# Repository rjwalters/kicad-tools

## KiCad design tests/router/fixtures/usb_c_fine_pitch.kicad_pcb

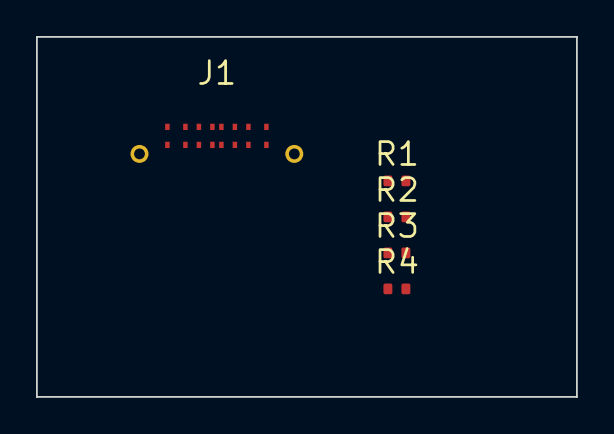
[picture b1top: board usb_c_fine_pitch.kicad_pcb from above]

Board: 4 copper layers, 30.0 x 20.0 mm, 5 parts (0 on the bottom side), 6 nets, no tracks yet.

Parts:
J1: USB-C; USB_C_Receptacle_GCT_USB4105
R1, R2: 0R; R_0402_1005Metric
R3, R4: 5k1; R_0402_1005Metric

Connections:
GND: J1.A1, J1.A12, J1.B1, J1.B12, J1.S1, J1.S2, R3.2, R4.2
USB_CC1: J1.A5, R3.1
USB_CC2: J1.B5, R4.1
USB_D+: J1.A6, J1.B6, R1.1
USB_D-: J1.A7, J1.B7, R2.1
VBUS: J1.A4, J1.A9, J1.B4, J1.B9
